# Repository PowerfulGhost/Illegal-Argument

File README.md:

# Illegal-Argument
**(WIP)**
有两个摇杆的40%人体工程学分体键盘

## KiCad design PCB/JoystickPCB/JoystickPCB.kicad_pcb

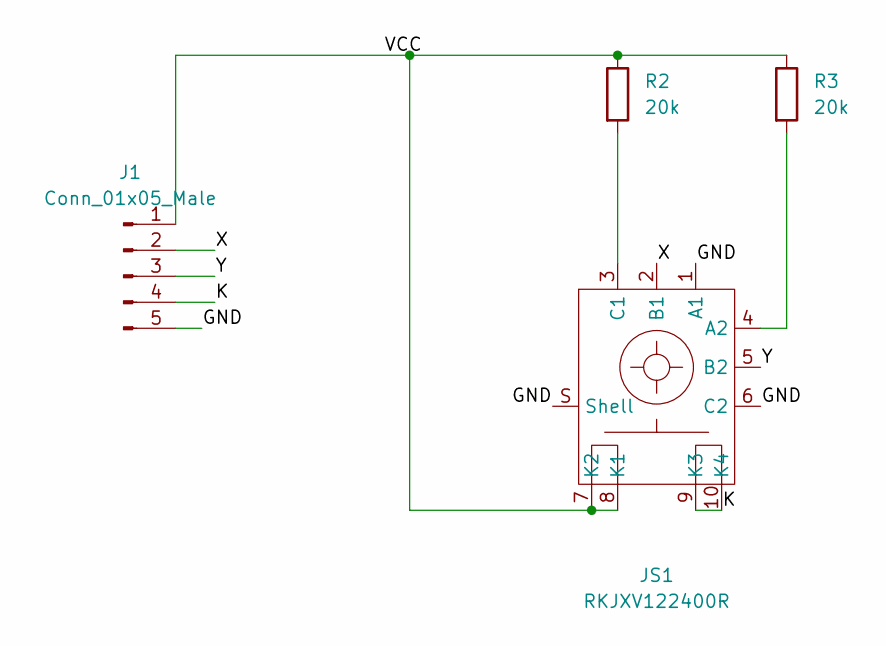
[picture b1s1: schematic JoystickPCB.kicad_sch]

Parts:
J1: Conn_01x05_Male; PinHeader_1x05_P2.54mm_Vertical
JS1: RKJXV122400R; MPN RKJXV122400R
R2, R3: 20k; R_Axial_DIN0207_L6.3mm_D2.5mm_P7.62mm_Horizontal

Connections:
/GND: J1.5, JS1.1 (A1), JS1.6 (C2), JS1.S (Shell)
/K: J1.4, JS1.9 (K3), JS1.10 (K4)
/VCC: J1.1, JS1.7 (K2), JS1.8 (K1), R2.1, R3.1
/X: J1.2, JS1.2 (B1)
/Y: J1.3, JS1.5 (B2)
unnamed: JS1.3 (C1), R2.2
unnamed: JS1.4 (A2), R3.2

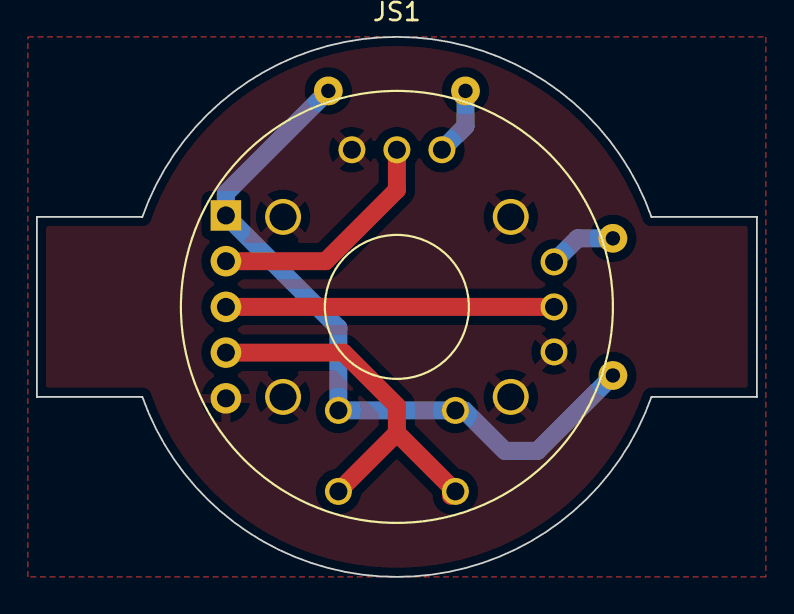
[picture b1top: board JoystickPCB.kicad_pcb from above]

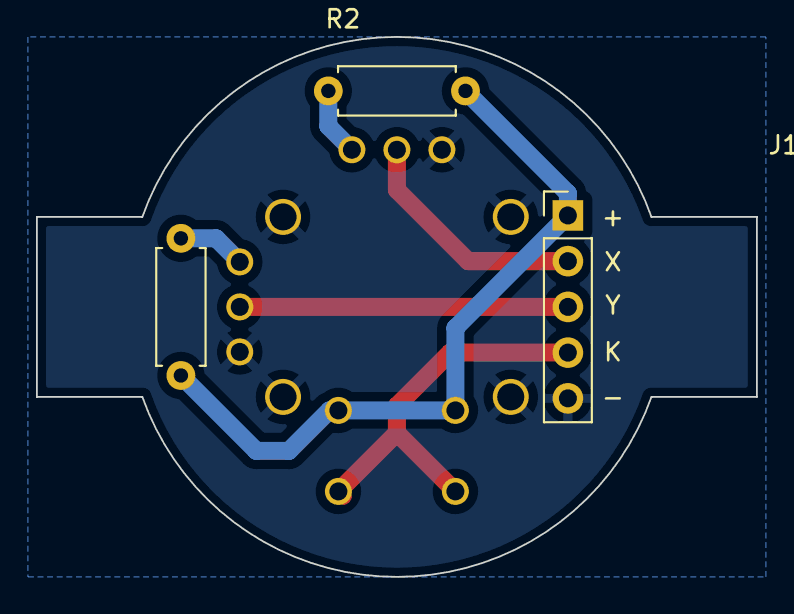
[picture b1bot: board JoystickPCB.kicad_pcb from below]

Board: 2 copper layers, 40.0 x 30.0 mm, 4 parts (3 on the bottom side), 7 nets.

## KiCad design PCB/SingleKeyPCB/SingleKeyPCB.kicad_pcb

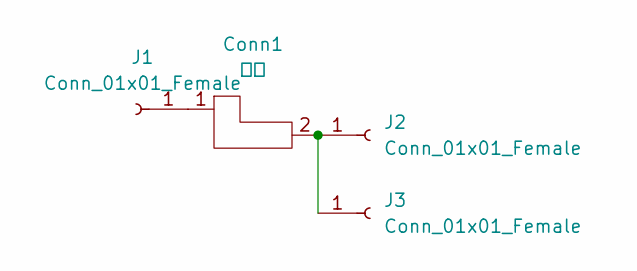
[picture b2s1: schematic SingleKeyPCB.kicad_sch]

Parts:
Conn1: 轴座; 五脚轴座; MPN CPG151101S51
J1, J2, J3: Conn_01x01_Female; SolderWire-0.25sqmm_1x01_D0.65mm_OD1.7mm

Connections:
unnamed: Conn1.1, J1.1
unnamed: Conn1.2, J2.1, J3.1

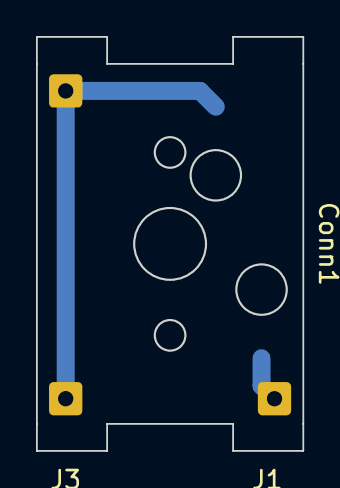
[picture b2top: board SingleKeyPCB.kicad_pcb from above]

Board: 2 copper layers, 14.8 x 23.0 mm, 4 parts (0 on the bottom side), 2 nets.

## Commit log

2023-05-08 create readme file
2023-05-08 首次提交
2023-05-19 增加摇杆pcb
2023-05-19 增加摇杆安装结构
2023-05-19 把底座上的Support0Slider改为单轨而非双轨
2023-05-19 新增了无名指和小指的keyholder，稍微探索了一下大拇指按键组的排列
2023-05-20 把底座竖着的导轨改为双轨，把support1和support2改为单轨，增加了螺丝帽模型
2023-05-20 把Support0Slider底部加厚1mm，使其能够贴合桌面
2023-05-23 增加了可打印的轴芯的模型
2023-06-09 增加了拇指按键组和电路部分的安装结构，结构设计工作基本完成了
